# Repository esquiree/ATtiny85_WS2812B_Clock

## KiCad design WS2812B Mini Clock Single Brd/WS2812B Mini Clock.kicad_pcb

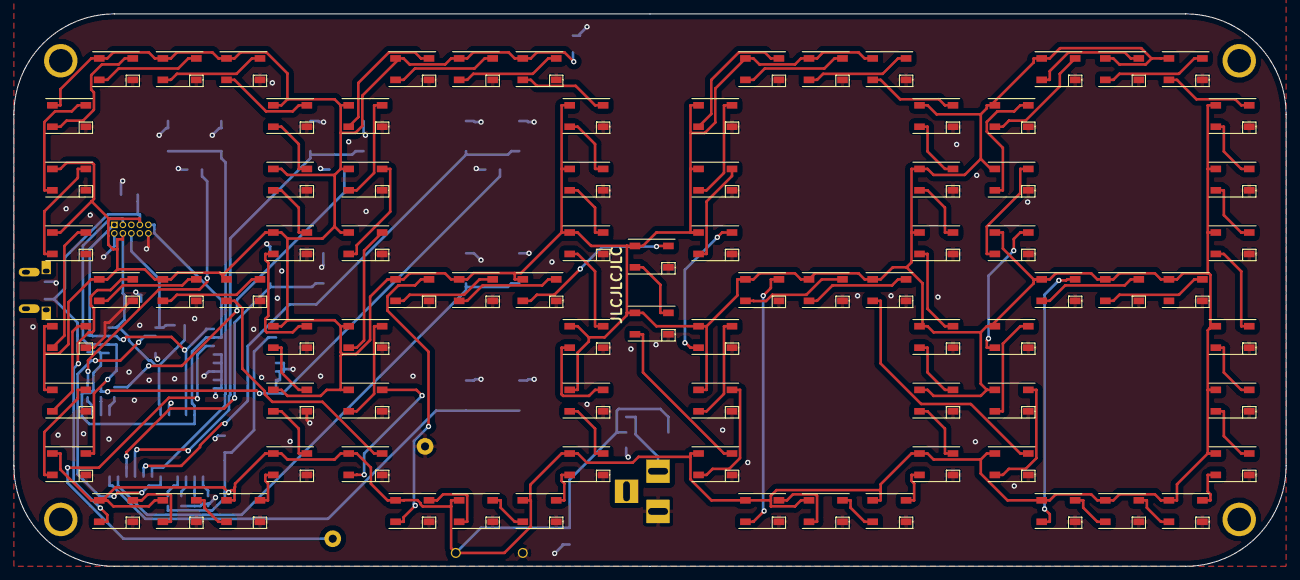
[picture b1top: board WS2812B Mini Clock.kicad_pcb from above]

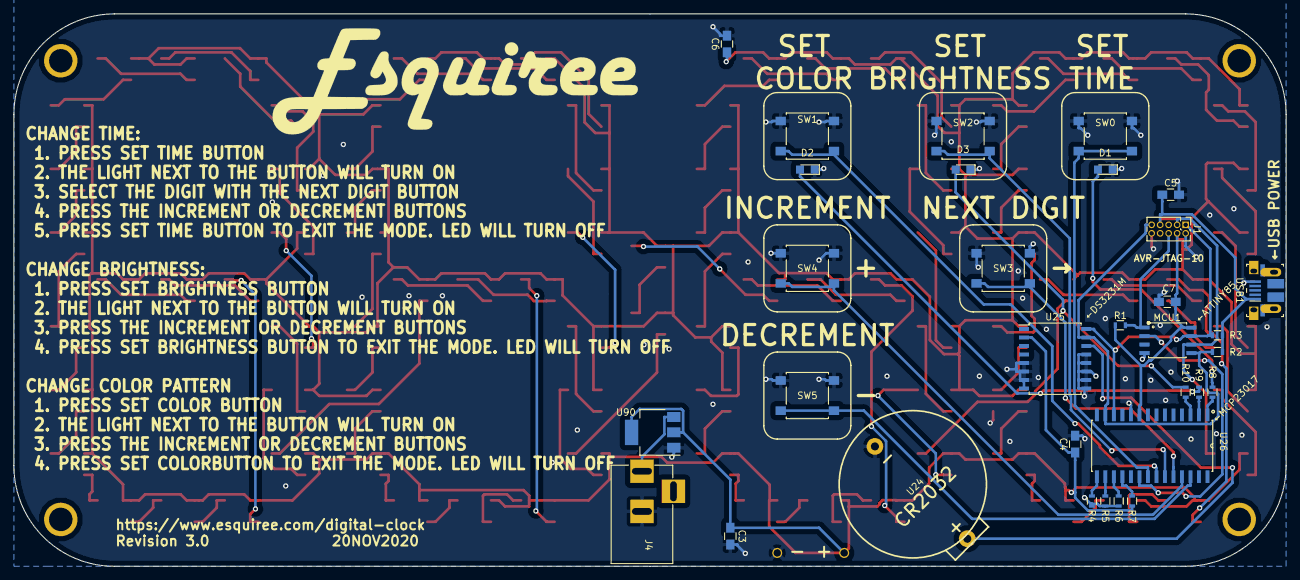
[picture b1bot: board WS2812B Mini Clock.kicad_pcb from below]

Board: 2 copper layers, 190.0 x 82.5 mm, 123 parts (32 on the bottom side), 110 nets.

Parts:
C3, C4, C5, C6, C7: 0.1uF; C_0805_HandSoldering
D1, D2, D3: LED; LED_0805
J1: AVR-JTAG-10; Pin_Header_Straight_2x05_Pitch1.27mm
J2, J3: Conn_01x01; 1mm Mount
J4: Barrel_Jack; BARREL_JACK
MCU1: ATtiny85-20SU; ATtiny85_SMD
R1, R2, R3, R4, R5, R6, R7: 10k; R_0603
R8, R9, R10: 1k; R_0603
REF2, REF3, REF4: 4mm Mount
SW0, SW1, SW2, SW3, SW4, SW5: SW_Push; SW_SPST_B3S-1000
U1, U2, U3, U4, U5, U6, U7, U8, U9, U10, U11, U12, U13, U14, U15, U16, U17, U18, U19, U20, U21, U22, U23, U27, U28, U29, U30, U31, U32, U33, U34, U35, U36, U37, U38, U39, U40, U41, U42, U43, U44, U45, U46, U47, U48, U49, U50, U51, U52, U53, U54, U55, U56, U57, U58, U59, U60, U61, U62, U63, U64, U65, U66, U67, U68, U69, U70, U71, U72, U73, U74, U75, U76, U77, U78, U79, U80, U81, U82, U83, U84, U85, U86, U87, U88, U89: WS2812B; WS2812B_Ver2_INV
U24: Bat; CR2032 Housing
U25: DS3231M; SOIC-16W_7.5x10.3mm_Pitch1.27mm
U26: MCP23017T-E_SO; SOIC127P1030X265-28N
U90: AZ1117-5.0; SOT-223-3_TabPin2
USB1: USB_B_Micro; USB_Micro_B_Female_10103594-0001LF

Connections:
+5V: C3.1, C4.1, C5.1, C6.1, C7.1, J1.4, J1.7, J2.1, MCU1.8, R1.1, R2.1, R3.1, R7.2, U1.1, U2.1, U3.1, U4.1, U5.1, U6.1, U7.1, U8.1, U9.1, U10.1, U11.1, U12.1, U13.1, U14.1, U15.1, U16.1, U17.1, U18.1, U19.1, U20.1, U21.1, U22.1, U23.1, U25.2, U26.9, U27.1, U28.1, U29.1, U30.1, U31.1, U32.1, U33.1, U34.1, U35.1, U36.1, U37.1, U38.1, U39.1, U40.1, U41.1, U42.1, U43.1, U44.1, U45.1, U46.1, U47.1, U48.1, U49.1, U50.1, U51.1, U52.1, U53.1, U54.1, U55.1, U56.1, U57.1, U58.1, U59.1, U60.1, U61.1, U62.1, U63.1, U64.1, U65.1, U66.1, U67.1, U68.1, U69.1, U70.1, U71.1, U72.1, U73.1, U74.1, U75.1, U76.1, U77.1, U78.1, U79.1, U80.1, U81.1, U82.1, U83.1, U84.1, U85.1, U86.1, U87.1, U88.1, U89.1, U90.2, USB1.1
BTN0: SW0.1, U26.21
BTN1: SW1.1, U26.22
BTN2: SW2.1, U26.23
BTN3: SW3.1, U26.24
BTN4: SW4.1, U26.25
BTN5: SW5.1, U26.26
DIN: J1.3, MCU1.6, U1.4
DOUT: U47.2, U48.4
GND: C3.2, C4.2, C5.2, C6.2, C7.2, D1.1, D2.1, D3.1, J1.2, J1.10, J3.1, J4.2, MCU1.4, R4.2, R5.2, R6.2, SW0.2, SW1.2, SW2.2, SW3.2, SW4.2, SW5.2, U1.3, U2.3, U3.3, U4.3, U5.3, U6.3, U7.3, U8.3, U9.3, U10.3, U11.3, U12.3, U13.3, U14.3, U15.3, U16.3, U17.3, U18.3, U19.3, U20.3, U21.3, U22.3, U23.3, U24.1, U25.5, U25.6, U25.7, U25.8, U25.9, U25.10, U25.11, U25.12, U25.13, U26.10, U27.3, U28.3, U29.3, U30.3, U31.3, U32.3, U33.3, U34.3, U35.3, U36.3, U37.3, U38.3, U39.3, U40.3, U41.3, U42.3, U43.3, U44.3, U45.3, U46.3, U47.3, U48.3, U49.3, U50.3, U51.3, U52.3, U53.3, U54.3, U55.3, U56.3, U57.3, U58.3, U59.3, U60.3, U61.3, U62.3, U63.3, U64.3, U65.3, U66.3, U67.3, U68.3, U69.3, U70.3, U71.3, U72.3, U73.3, U74.3, U75.3, U76.3, U77.3, U78.3, U79.3, U80.3, U81.3, U82.3, U83.3, U84.3, U85.3, U86.3, U87.3, U88.3, U89.3, U90.1, USB1.5
INT: MCU1.2, U26.20
LED0: R8.2, U26.1
LED1: R9.2, U26.2
LED2: R10.2, U26.3
unnamed: D1.2, R8.1
unnamed: D2.2, R9.1
unnamed: D3.2, R10.1
unnamed: J4.1, U90.3
unnamed: R4.1, U26.15
unnamed: R5.1, U26.16
unnamed: R6.1, U26.17
unnamed: R7.1, U26.18
unnamed: U1.2, U2.4
unnamed: U2.2, U3.4
unnamed: U3.2, U4.4
unnamed: U4.2, U5.4
unnamed: U5.2, U6.4
unnamed: U6.2, U7.4
unnamed: U7.2, U8.4
unnamed: U8.2, U9.4
unnamed: U10.2, U11.4
unnamed: U9.2, U10.4
unnamed: U11.2, U12.4
unnamed: U12.2, U13.4
unnamed: U13.2, U14.4
unnamed: U14.2, U15.4
unnamed: U15.2, U16.4
unnamed: U16.2, U17.4
unnamed: U17.2, U18.4
unnamed: U18.2, U19.4
unnamed: U19.2, U20.4
unnamed: U20.2, U21.4
unnamed: U21.2, U22.4
unnamed: U22.2, U23.4
unnamed: U23.2, U27.4
unnamed: U24.2, U25.14
unnamed: U27.2, U28.4
unnamed: U28.2, U29.4
unnamed: U29.2, U30.4
unnamed: U30.2, U31.4
unnamed: U31.2, U32.4
unnamed: U32.2, U33.4
unnamed: U33.2, U34.4
unnamed: U34.2, U35.4
unnamed: U35.2, U36.4
unnamed: U36.2, U37.4
unnamed: U37.2, U38.4
unnamed: U38.2, U39.4
unnamed: U39.2, U40.4
unnamed: U40.2, U41.4
unnamed: U41.2, U42.4
unnamed: U42.2, U43.4
unnamed: U43.2, U44.4
unnamed: U44.2, U45.4
unnamed: U45.2, U46.4
unnamed: U46.2, U47.4
unnamed: U48.2, U53.4
unnamed: U49.2, U54.4
unnamed: U49.4, U58.2
unnamed: U50.2, U55.4
unnamed: U50.4, U59.2
unnamed: U51.2, U56.4
unnamed: U51.4, U60.2
unnamed: U52.2, U57.4
unnamed: U52.4, U61.2
unnamed: U53.2, U58.4
unnamed: U54.2, U59.4
unnamed: U55.2, U60.4
unnamed: U56.2, U61.4
unnamed: U57.2, U62.4
unnamed: U62.2, U63.4
unnamed: U63.2, U68.4
unnamed: U64.2, U69.4
unnamed: U64.4, U73.2
unnamed: U65.2, U70.4
unnamed: U65.4, U74.2
unnamed: U66.2, U71.4
unnamed: U66.4, U75.2
unnamed: U67.2, U72.4
unnamed: U67.4, U76.2
unnamed: U68.2, U73.4
unnamed: U69.2, U74.4
unnamed: U70.2, U75.4
unnamed: U71.2, U76.4
unnamed: U72.2, U77.4
unnamed: U77.2, U78.4
unnamed: U78.2, U82.4
unnamed: U79.2, U83.4
unnamed: U79.4, U86.2
unnamed: U80.2, U84.4
unnamed: U80.4, U87.2
unnamed: U81.2, U85.4
unnamed: U81.4, U88.2
unnamed: U82.2, U86.4
unnamed: U83.2, U87.4
unnamed: U84.2, U88.4
unnamed: U85.2, U89.4
RST: J1.6, MCU1.1, R1.2
SCL: J1.1, MCU1.7, R3.2, U25.16, U26.12
SDA: J1.9, MCU1.5, R2.2, U25.15, U26.13

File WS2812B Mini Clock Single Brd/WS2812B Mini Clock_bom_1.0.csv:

Component,Description,Part,References,Value,Footprint,Quantity Per PCB,Datasheet,STANDARD,MANUFACTURER,MPN
1,Unpolarized capacitor,C,C3 C4 C5 C6 C7,0.1uF,C_0805_HandSoldering,5,~,,,
2,LED generic,LED,D1 D2 D3,LED,LED_0805,3,~,,,
3,Atmel 10-pin JTAG connector,AVR-JTAG-10,J1,AVR-JTAG-10,Pin_Header_Straight_2x05_Pitch1.27mm,1, ~,,,
4,DC Barrel Jack,Barrel_Jack,J4,Barrel_Jack,BARREL_JACK,1,~,,,
5,"Generic connector, single row, 01x01, script generated (kicad-library-utils/schlib/autogen/connector/)",Conn_01x01,J2 J3,Conn_01x01,1mm Mount,2,~,,,
6,"20MHz, 8kB Flash, 512B SRAM, 512B EEPROM, debugWIRE, DIP-8",ATtiny85-20PU,MCU1,ATtiny85-20SU,ATtiny85_SMD,1,http://ww1.microchip.com/downloads/en/DeviceDoc/atmel-2586-a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,,,
7,Resistor,R,R1 R2 R3 R4 R5 R6 R7,10k,R_0603,7,~,,,
8,Resistor,R,R8 R9 R10,1k,R_0603,3,~,,,
9,"Push button switch, generic, two pins",SW_Push,SW0 SW1 SW2 SW3 SW4 SW5,SW_Push,SW_SPST_B3S-1000,6,,,,
10,"1A 20V Fixed LDO Linear Regulator, 5.0V, SOT-89/SOT-223/TO-220/TO-252/TO-263",AZ1117-5.0,U90,AZ1117-5.0,SOT-223-3_TabPin2,1,https://www.diodes.com/assets/Datasheets/AZ1117.pdf,,,
11,,Bat,U24,Bat,CR2032 Housing,1,,,,
12,Extremely Accurate I2C-Integrated RTC/TCXO/Crystal SOIC-16,DS3231M,U25,DS3231M,SOIC-16W_7.5x10.3mm_Pitch1.27mm,1,http://datasheets.maximintegrated.com/en/ds/DS3231.pdf,,,
13,,MCP23017T-E_SO,U26,MCP23017T-E_SO,SOIC127P1030X265-28N,1,,IPC7351B,Microchip,
14,,WS2812B,U1 U2 U3 U4 U5 U6 U7 U8 U9 U10 U11 U12 U13 U14 U15 U16 U17 U18 U19 U20 U21 U22 U23 U27 U28 U29 U30 U31 U32 U33 U34 U35 U36 U37 U38 U39 U40 U41 U42 U43 U44 U45 U46 U47 U48 U49 U50 U51 U52 U53 U54 U55 U56 U57 U58 U59 U60 U61 U62 U63 U64 U65 U66 U67 U68 U69 U70 U71 U72 U73 U74 U75 U76 U77 U78 U79 U80 U81 U82 U83 U84 U85 U86 U87 U88 U89,WS2812B,WS2812B-MINI,86,,,,
15,USB Micro Type B connector,USB_B_Micro,USB1,USB_B_Micro,USB_Micro_B_Female_10103594-0001LF,1,~,,,0473460001





Component Groups:,15
Component Count:,120
Fitted Components:,120
Number of PCBs:,1
Total components:,120
Schematic Version:,1.0
Schematic Date:,2020-11-19
BoM Date:,11/20/2020 22:12:04
Schematic Source:,C:\Users\Reed\Documents\WS2812B Mini Clock Single Brd\WS2812B Mini Clock.sch
KiCad Version:,Eeschema (5.0.0)

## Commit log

2020-10-01 Rev B PCB Files
2020-10-01 Rev B Code. Uses ATtiny85
